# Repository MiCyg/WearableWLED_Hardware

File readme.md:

# Wearable WLED Hardware

[← Back to main repository](https://github.com/MiCyg/WearableWLED.git)

---

This PCB combines an ESP32‑C3 Mini with a battery charger, a power switch, and a USB‑C connector for power and programming. All components are low‑cost and readily available. The PCB measures 20×40 mm, allowing a compact enclosure and battery.

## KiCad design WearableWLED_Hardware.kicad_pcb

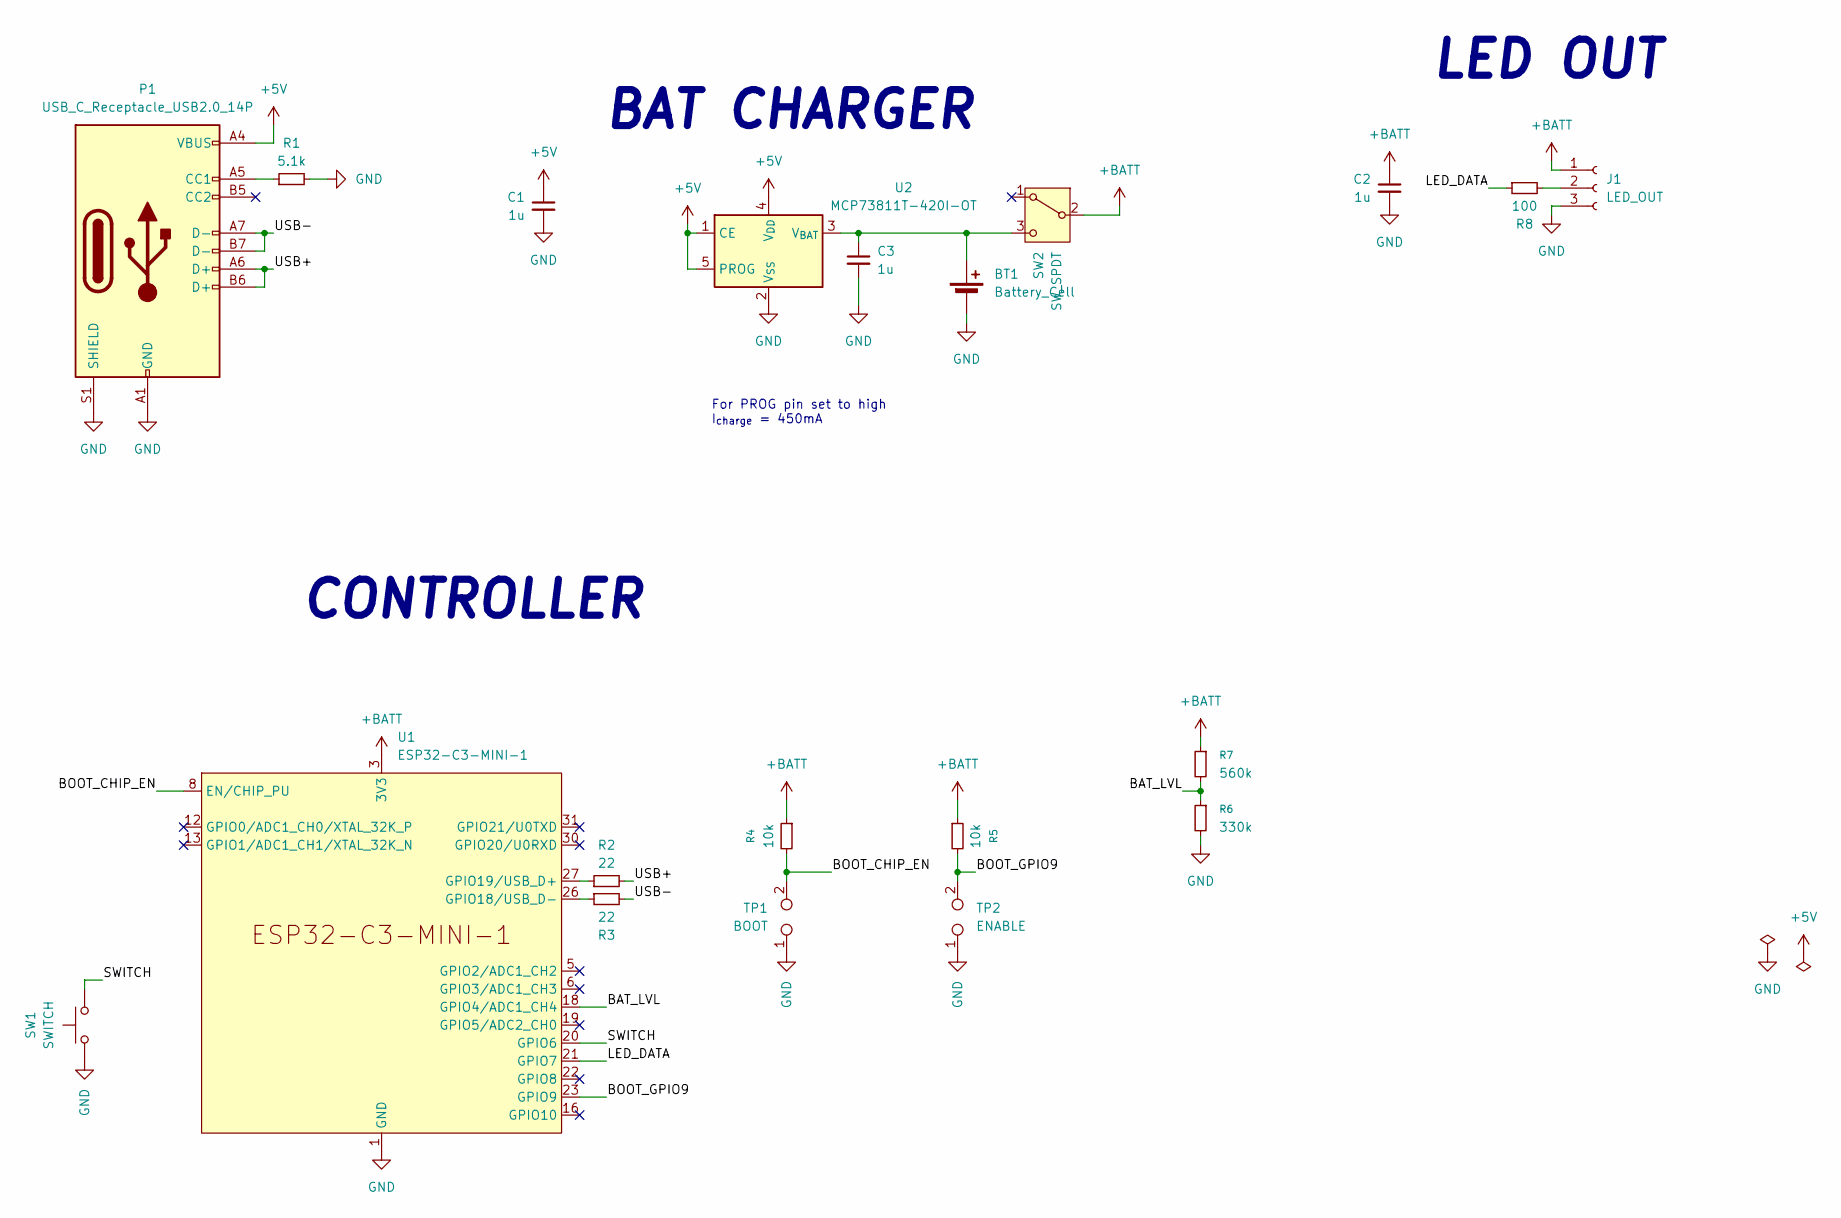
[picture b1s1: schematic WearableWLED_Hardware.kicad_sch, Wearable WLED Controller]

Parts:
BT1: Battery_Cell; Molex_PicoBlade_53047-0210_1x02_P1.25mm_Vertical
C1, C2, C3: 1u; C_0603_1608Metric_Pad1.08x0.95mm_HandSolder
J1: LED_OUT; PinSocket_1x03_P2.54mm_Vertical
P1: USB_C_Receptacle_USB2.0_14P; USB_C_Receptacle_G-Switch_GT-USB-7010ASV
R1: 5.1k; R_0603_1608Metric_Pad0.98x0.95mm_HandSolder
R2, R3: 22; R_0603_1608Metric_Pad0.98x0.95mm_HandSolder
R4, R5: 10k; R_0603_1608Metric_Pad0.98x0.95mm_HandSolder
R6: 330k; R_0603_1608Metric_Pad0.98x0.95mm_HandSolder
R7: 560k; R_0603_1608Metric_Pad0.98x0.95mm_HandSolder
R8: 100; R_0603_1608Metric_Pad0.98x0.95mm_HandSolder
SW1: SWITCH; SW_SPST_CK_RS282G05A3
SW2: SW_SPDT; SW_SPDT_Shouhan_MSK12C02
TP1: BOOT; SolderJumper-2_P1.3mm_Open_RoundedPad1.0x1.5mm
TP2: ENABLE; SolderJumper-2_P1.3mm_Open_RoundedPad1.0x1.5mm
U1: ESP32-C3-MINI-1
U2: MCP73811T-420I-OT; SOT-23-5

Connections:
+5V: C1.1, P1.A4 (VBUS), P1.A9 (VBUS), P1.B4 (VBUS), P1.B9 (VBUS), U2.1 (CE), U2.4 (V_{DD}), U2.5 (PROG)
+BATT: C2.1, J1.1, R4.1, R5.1, R7.1, SW2.2 (B), U1.3 (3V3)
/BAT_LVL: R6.1, R7.2, U1.18 (GPIO4/ADC1_CH4)
/BOOT_CHIP_EN: R4.2, TP1.2, U1.8 (EN/CHIP_PU)
/BOOT_GPIO9: R5.2, TP2.2, U1.23 (GPIO9)
/LED_DATA: R8.1, U1.21 (GPIO7)
/SWITCH: SW1.2, U1.20 (GPIO6)
/USB+: P1.A6 (D+), P1.B6 (D+), R2.2
/USB-: P1.A7 (D-), P1.B7 (D-), R3.2
GND: BT1.2 (-), C1.2, C2.2, C3.2, J1.3, P1.A1 (GND), P1.A12 (GND), P1.B1 (GND), P1.B12 (GND), P1.S1 (SHIELD), R1.2, R6.2, SW1.1, TP1.1, TP2.1, U1.1 (GND), U1.2 (GND), U1.11 (GND), U1.14 (GND), U1.36 (GND), U1.37 (GND), U1.38 (GND), U1.39 (GND), U1.40 (GND), U1.41 (GND), U1.42 (GND), U1.43 (GND), U1.44 (GND), U1.45 (GND), U1.46 (GND), U1.47 (GND), U1.48 (GND), U1.49 (GND), U1.50 (GND), U1.51 (GND), U1.52 (GND), U1.53 (GND), U2.2 (V_{SS})
unnamed: BT1.1 (+), C3.1, SW2.3 (C), U2.3 (V_{BAT})
unnamed: J1.2, R8.2
unnamed: P1.A5 (CC1), R1.1
unnamed: R3.1, U1.26 (GPIO18/USB_D-)
unnamed: R2.1, U1.27 (GPIO19/USB_D+)

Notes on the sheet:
LED OUT
For PROG pin set to high I_{charge} = 450mA
CONTROLLER
BAT CHARGER

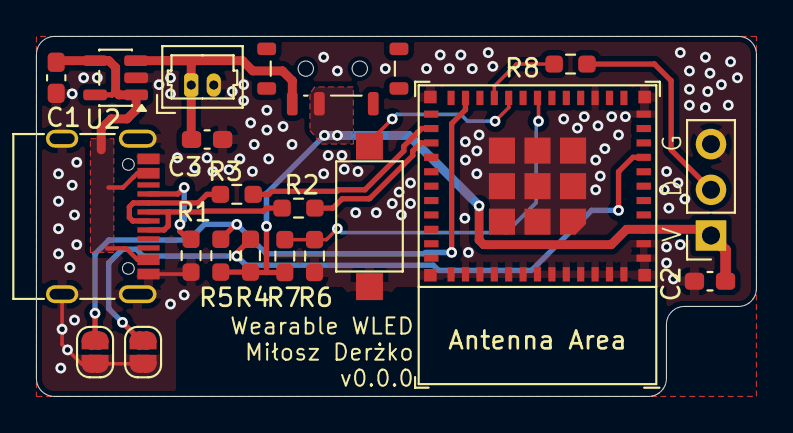
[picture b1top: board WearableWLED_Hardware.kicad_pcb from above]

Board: 2 copper layers, 40.0 x 20.0 mm, 20 parts (0 on the bottom side), 15 nets.

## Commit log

2025-12-23 chore: init repo
2026-02-06 Change voltage divider value for battery
2026-02-06 doc: Add pdfs and images
2026-02-06 doc: Update readme
2026-02-07 doc: Update images and readme
